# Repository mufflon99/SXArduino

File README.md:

# SX2Arduino
Lesen und Schreiben von SX1, SX2 und DCC Loks,
basiert auf der Libary von Gerard van der Sel.
Für das SX2 Interface wird ein Arduino Mega oder Arduino Due benötigt.
Serrvo Decoder zum Einbau in Signalschacht mit Arduino Nano
(SX is an open Model Railroad Control System, standardized in NEM 680 and NEM 681, Selectrix is a Trademark of TRIX - now owned by Maerklin)

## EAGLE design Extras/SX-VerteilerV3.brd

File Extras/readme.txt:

Für denen Nano Servo Decoder wird die Einspeise Platine SX Verteiler benötigt.

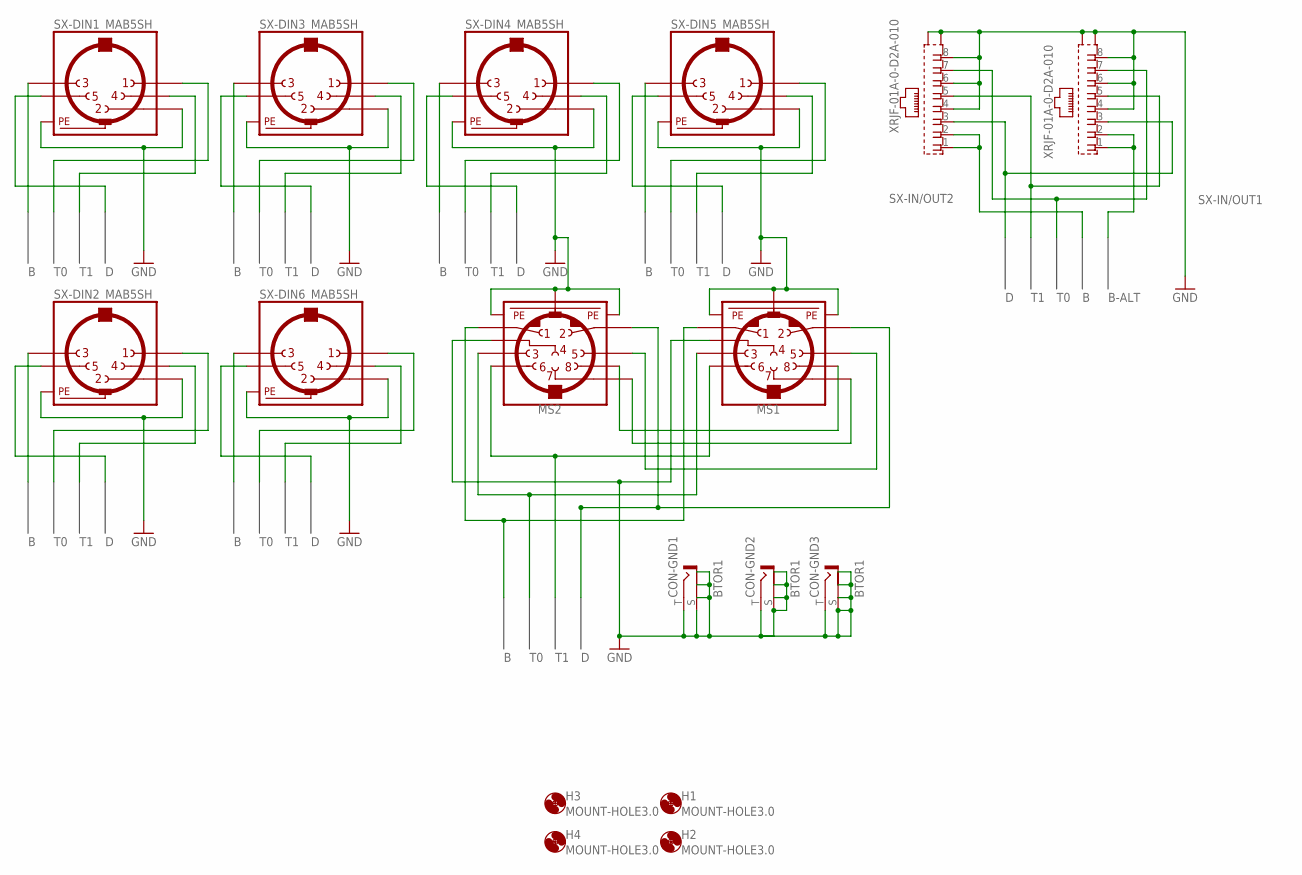
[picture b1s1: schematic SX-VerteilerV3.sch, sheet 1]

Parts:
CON-GND1, CON-GND2, CON-GND3: BTOR1
H1, H2, H3, H4: MOUNT-HOLE3.0; 3,0
MS1, MS2: MINI_DIN_8; M_DIN8
SX-DIN1, SX-DIN2, SX-DIN3, SX-DIN4, SX-DIN5, SX-DIN6: MAB5SH
SX-IN/OUT1, SX-IN/OUT2: XRJF-01A-0-D2A-010

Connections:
B: MS1.1, MS2.1, SX-DIN1.3, SX-DIN2.3, SX-DIN3.3, SX-DIN4.3, SX-DIN5.3, SX-DIN6.3, SX-IN/OUT2.1, SX-IN/OUT2.2; also elsewhere on the board
B-ALT: SX-IN/OUT1.1, SX-IN/OUT1.2; also elsewhere on the board
D: MS1.2, MS2.2, SX-DIN1.5, SX-DIN2.5, SX-DIN3.5, SX-DIN4.5, SX-DIN5.5, SX-DIN6.5, SX-IN/OUT1.3, SX-IN/OUT2.3; also elsewhere on the board
GND: CON-GND1.S (2), CON-GND1.S@1 (2), CON-GND1.S@2 (2), CON-GND1.S@3 (2), CON-GND1.T (1), CON-GND2.S (2), CON-GND2.S@1 (2), CON-GND2.S@2 (2), CON-GND2.S@3 (2), CON-GND2.T (1), CON-GND3.S (2), CON-GND3.S@1 (2), CON-GND3.S@2 (2), CON-GND3.S@3 (2), CON-GND3.T (1), MS1.4, MS1.SH1 (PE1), MS1.SH2 (PE2), MS1.SH3 (PE3), MS2.4, MS2.SH1 (PE1), MS2.SH2 (PE2), MS2.SH3 (PE3), SX-DIN1.2, SX-DIN1.PE, SX-DIN1.PE@ (PE), SX-DIN2.2, SX-DIN2.PE, SX-DIN2.PE@ (PE), SX-DIN3.2, SX-DIN3.PE, SX-DIN3.PE@ (PE), SX-DIN4.2, SX-DIN4.PE, SX-DIN4.PE@ (PE), SX-DIN5.2, SX-DIN5.PE, SX-DIN5.PE@ (PE), SX-DIN6.2, SX-DIN6.PE, SX-DIN6.PE@ (PE), SX-IN/OUT1.4, SX-IN/OUT1.6, SX-IN/OUT1.8, SX-IN/OUT1.S1 (S), SX-IN/OUT1.S2 (S), SX-IN/OUT2.4, SX-IN/OUT2.6, SX-IN/OUT2.8, SX-IN/OUT2.S1 (S), SX-IN/OUT2.S2 (S); also elsewhere on the board
unnamed: MS1.8, MS2.8
unnamed: MS1.7, MS2.7
unnamed: MS1.5, MS2.5
T0: MS1.3, MS2.3, SX-DIN1.1, SX-DIN2.1, SX-DIN3.1, SX-DIN4.1, SX-DIN5.1, SX-DIN6.1, SX-IN/OUT1.7, SX-IN/OUT2.7; also elsewhere on the board
T1: MS1.6, MS2.6, SX-DIN1.4, SX-DIN2.4, SX-DIN3.4, SX-DIN4.4, SX-DIN5.4, SX-DIN6.4, SX-IN/OUT1.5, SX-IN/OUT2.5; also elsewhere on the board

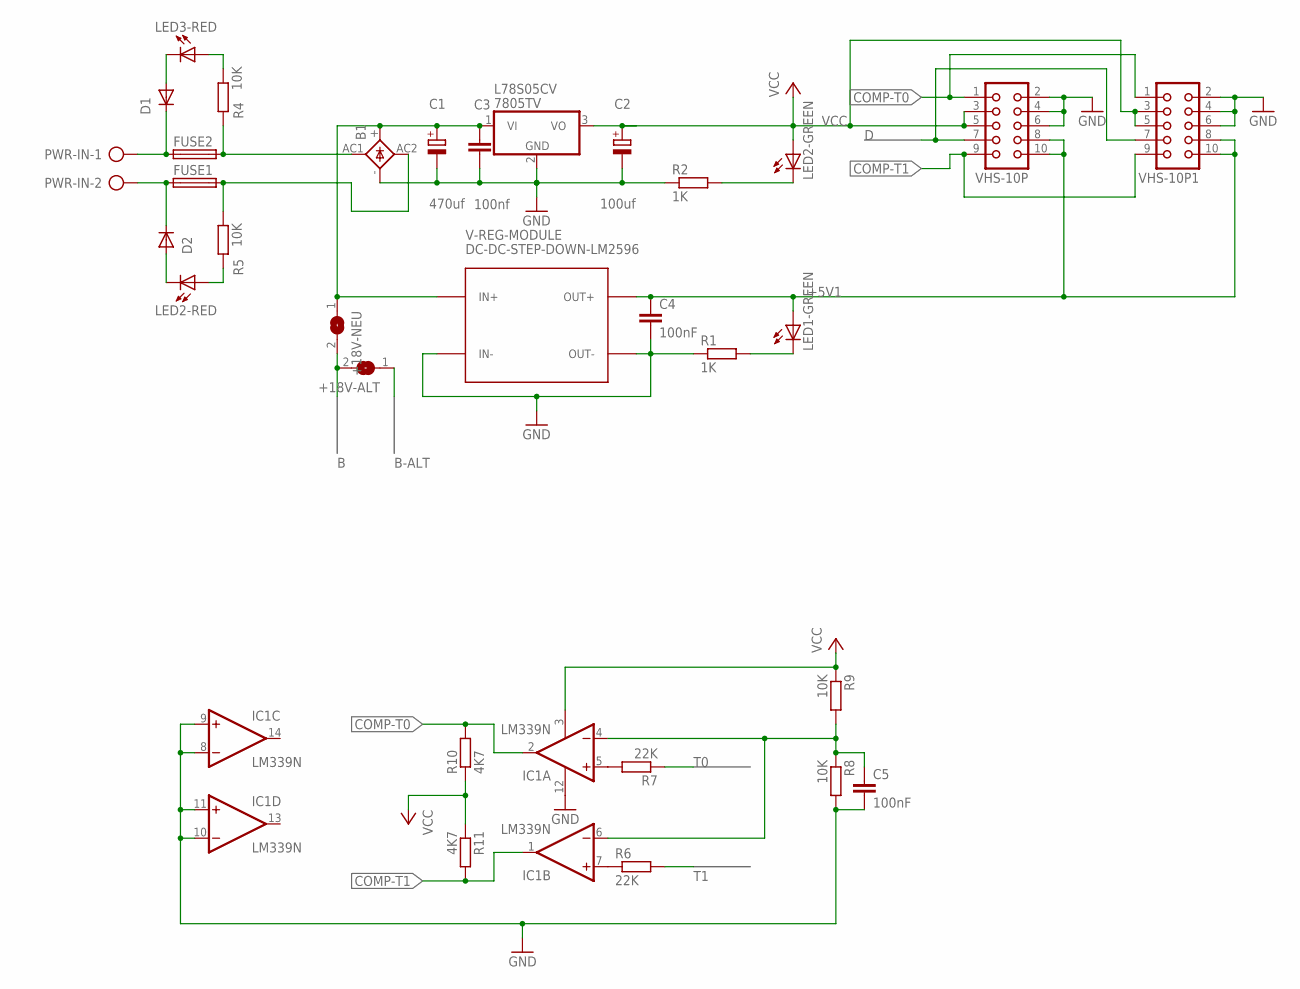
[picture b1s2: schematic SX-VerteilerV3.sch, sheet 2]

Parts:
+18V-ALT, +18V-NEU: SJW
B1: KBU
C1: 470uf; E5-13
C2: 100uf; E3,5-8
C3: 100nf; C0805
C4, C5: 100nF; C0805
D1, D2: PMLL4150; SOD80C
FUSE1, FUSE2: FUSEBLANK_5X20MM; FUSE_HOLDER_5X20MM
IC1: LM339N; DIL14
L78S05CV: 7805TV; TO220V
LED1-GREEN, LED2-GREEN, LED2-RED, LED3-RED: LED3MM
PWR-IN: AK300/2
R1, R2: 1K; R0805
R4, R5, R8, R9: 10K; R0805
R6, R7: 22K; R0805
R10, R11: 4K7; R0805
V-REG-MODULE: DC-DC-STEP-DOWN-LM2596
VHS-10P, VHS-10P1: CON10

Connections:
+5V1: C4.1, LED1-GREEN.A, V-REG-MODULE.OUT+, VHS-10P.8, VHS-10P.10, VHS-10P1.8, VHS-10P1.10
B: +18V-ALT.2, +18V-NEU.2; also elsewhere on the board
B-ALT: +18V-ALT.1; also elsewhere on the board
COMP-T0: IC1.2 (OUT), R10.2, VHS-10P.1, VHS-10P1.1
COMP-T1: IC1.1 (OUT), R11.2, VHS-10P.9, VHS-10P1.9
D: VHS-10P.7, VHS-10P1.7; also elsewhere on the board
GND: B1.-, C1.-, C2.-, C3.2, C4.2, C5.2, IC1.8 (-IN), IC1.9 (+IN), IC1.10 (-IN), IC1.11 (+IN), IC1.12 (GND), L78S05CV.2 (GND), R1.1, R2.1, R8.2, V-REG-MODULE.IN-, V-REG-MODULE.OUT-, VHS-10P.2, VHS-10P.4, VHS-10P.6, VHS-10P1.2, VHS-10P1.4, VHS-10P1.6; also elsewhere on the board
unnamed: D1.C, FUSE2.1, PWR-IN.1
unnamed: D2.C, FUSE1.1, PWR-IN.2
unnamed: B1.AC1, FUSE2.2, R4.1
unnamed: B1.AC2, FUSE1.2, R5.2
unnamed: D1.A, LED3-RED.K (C)
unnamed: IC1.5 (+IN), R7.2
unnamed: LED2-GREEN.K (C), R2.2
unnamed: IC1.7 (+IN), R6.1
unnamed: LED1-GREEN.K (C), R1.2
unnamed: LED3-RED.A, R4.2
unnamed: C5.1, IC1.4 (-IN), IC1.6 (-IN), R8.1, R9.2
unnamed: D2.A, LED2-RED.K (C)
unnamed: LED2-RED.A, R5.1
unnamed: +18V-NEU.1, B1.+, C1.+, C3.1, L78S05CV.1 (VI), V-REG-MODULE.IN+
T0: R7.1; also elsewhere on the board
T1: R6.2; also elsewhere on the board
VCC: C2.+, IC1.3 (V+), L78S05CV.3 (VO), LED2-GREEN.A, R9.1, R10.1, R11.1, VHS-10P.3, VHS-10P.5, VHS-10P1.3, VHS-10P1.5

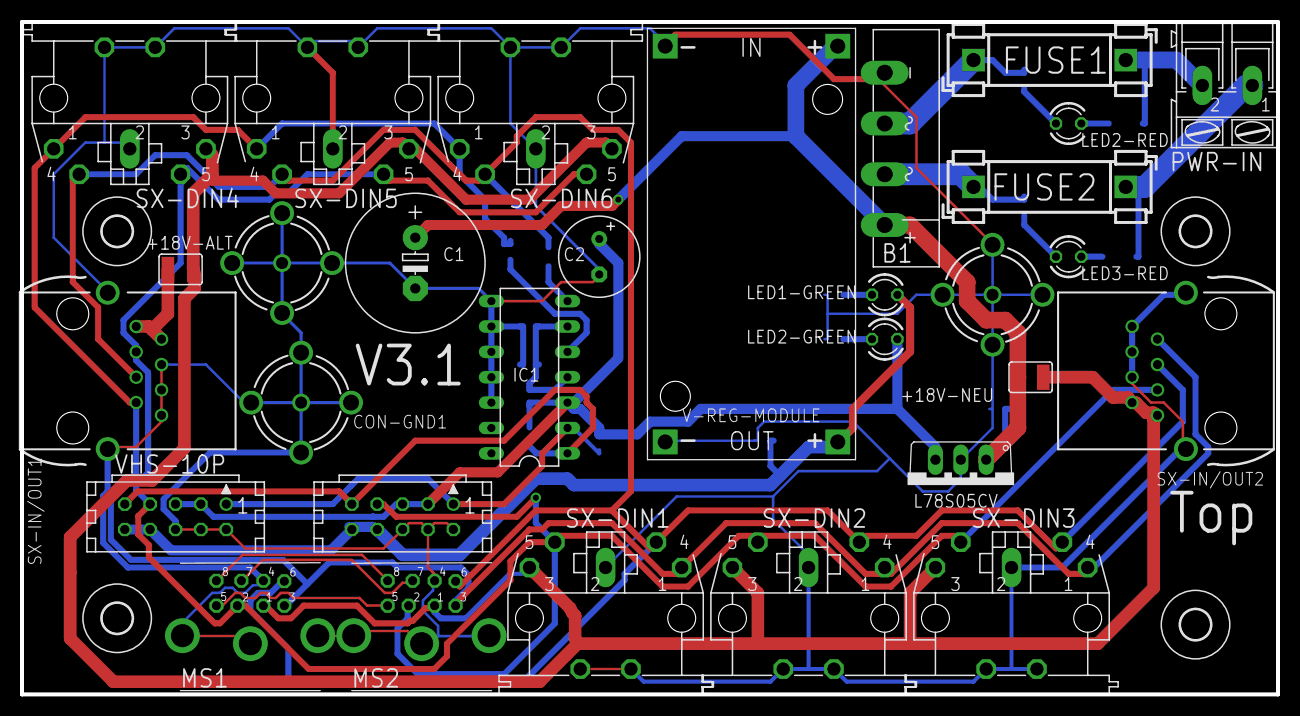
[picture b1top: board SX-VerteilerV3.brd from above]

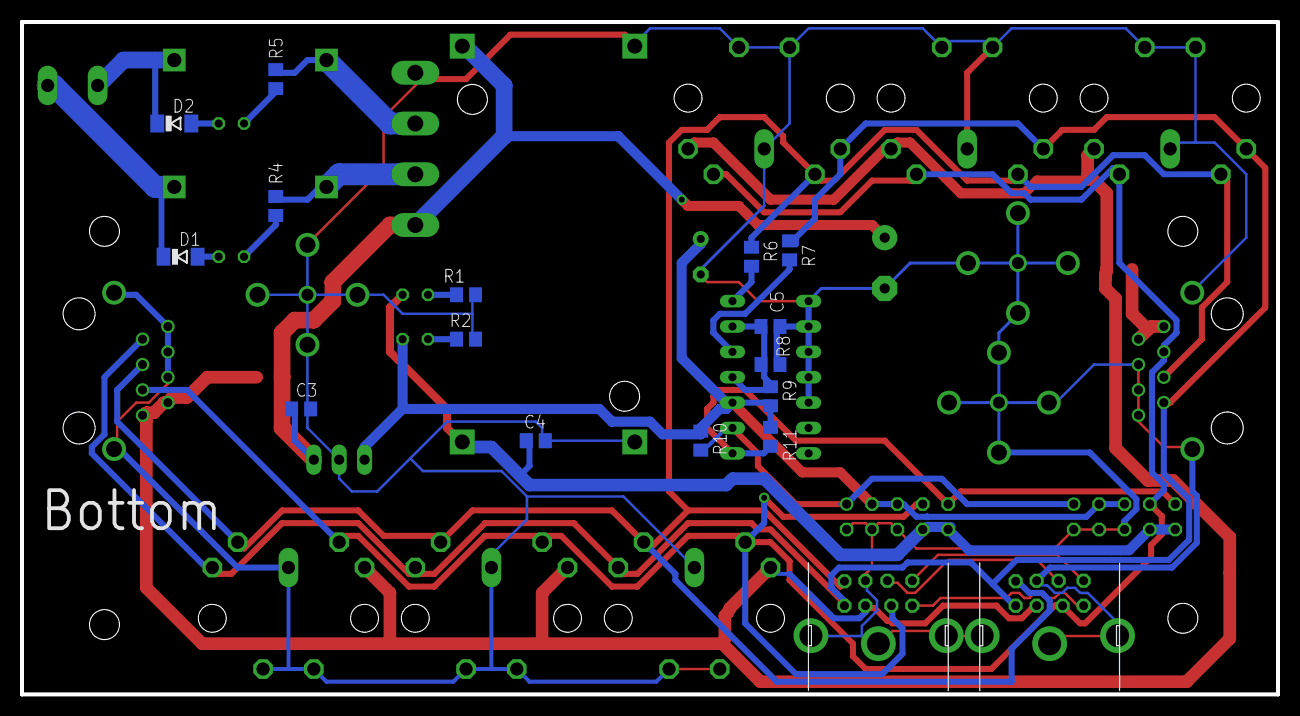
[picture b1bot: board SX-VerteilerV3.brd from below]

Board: 2 copper layers, 125.7 x 67.3 mm, 49 parts (15 on the bottom side), 27 nets.

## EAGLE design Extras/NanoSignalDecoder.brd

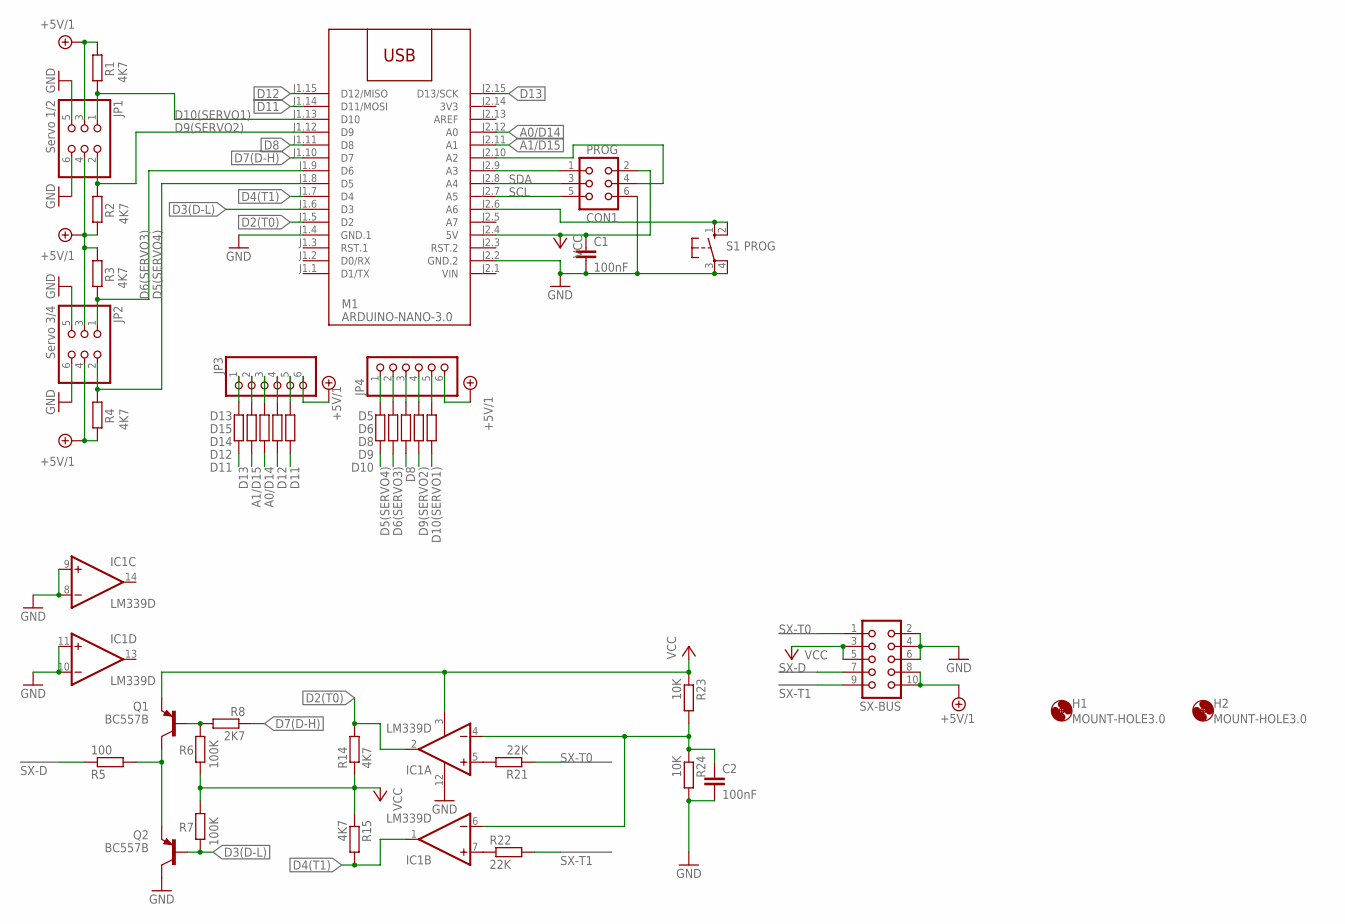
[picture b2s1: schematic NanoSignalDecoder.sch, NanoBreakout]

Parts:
C1, C2: 100nF; C0805
CON1: PROG; CON06
D5, D6, D8, D9, D10, D11, D12, D13, D14, D15: 500; R0805
H1, H2: MOUNT-HOLE3.0; 3,0
IC1: LM339D; SO14
JP1: Servo 1/2; 2X03/90
JP2: Servo 3/4; 2X03/90
JP3, JP4: PINHD-1X6; 1X06
M1: ARDUINO-NANO-3.0
Q1, Q2: BC557B; TO92-EBC
R1, R2, R3, R4, R14, R15: 4K7; R0805
R5: 100; R0805
R6, R7: 100K; R0805
R8: 2K7; R0805
R21, R22: 22K; R0805
R23, R24: 10K; R0805
S1: PROG; B3F-10XX
SX-BUS: CON10

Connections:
3V3: M1.J2.14 (3V3)
+5V/1: JP1.3, JP1.4, JP2.3, JP2.4, JP3.6, JP4.6, R1.1, R2.2, R3.1, R4.2, SX-BUS.8, SX-BUS.10
A0/D14: D14.1, M1.J2.12 (A0)
A1/D15: D15.1, M1.J2.11 (A1)
D2(T0): IC1.2 (OUT), M1.J1.5 (D2), R14.2
D3(D-L): M1.J1.6 (D3), Q2.B, R7.2
D4(T1): IC1.1 (OUT), M1.J1.7 (D4), R15.2
D5(SERVO4): D5.1, JP2.2, M1.J1.8 (D5), R4.1
D6(SERVO3): D6.1, JP2.1, M1.J1.9 (D6), R3.2
D7(D-H): M1.J1.10 (D7), R8.1
D8: D8.1, M1.J1.11 (D8)
D9(SERVO2): D9.1, JP1.2, M1.J1.12 (D9), R2.1
D10(SERVO1): D10.1, JP1.1, M1.J1.13 (D10), R1.2
D11: D11.1, M1.J1.14 (D11/MOSI)
D12: D12.1, M1.J1.15 (D12/MISO)
D13: D13.1, M1.J2.15 (D13/SCK)
GND: C1.2, C2.2, CON1.6, IC1.8 (-IN), IC1.9 (+IN), IC1.10 (-IN), IC1.11 (+IN), IC1.12 (GND), JP1.5, JP1.6, JP2.5, JP2.6, M1.J1.4 (GND.1), M1.J2.2 (GND.2), Q2.C, R24.2, S1.3, S1.4 (P1), SX-BUS.2, SX-BUS.4, SX-BUS.6
unnamed: D8.2, JP4.3
unnamed: D5.2, JP4.1
unnamed: D13.2, JP3.1
unnamed: D6.2, JP4.2
unnamed: D15.2, JP3.2
unnamed: C2.1, IC1.4 (-IN), IC1.6 (-IN), R23.2, R24.1
unnamed: Q1.C, Q2.E, R5.1
unnamed: D9.2, JP4.4
unnamed: D10.2, JP4.5
unnamed: D14.2, JP3.3
unnamed: D12.2, JP3.4
unnamed: D11.2, JP3.5
unnamed: Q1.B, R6.1, R8.2
unnamed: M1.J2.6 (A6), S1.1 (S), S1.2 (S1)
unnamed: CON1.1, M1.J2.9 (A3)
unnamed: CON1.4, M1.J2.10 (A2)
unnamed: IC1.5 (+IN), R21.2
unnamed: IC1.7 (+IN), R22.1
SCL: CON1.5, M1.J2.7 (A5)
SDA: CON1.3, M1.J2.8 (A4)
SX-D: R5.2, SX-BUS.7
SX-T0: R21.1, SX-BUS.1
SX-T1: R22.2, SX-BUS.9
VCC: C1.1, CON1.2, IC1.3 (V+), M1.J2.4 (5V), Q1.E, R6.2, R7.1, R14.1, R15.1, R23.1, SX-BUS.3, SX-BUS.5
VIN: M1.J2.1 (VIN)

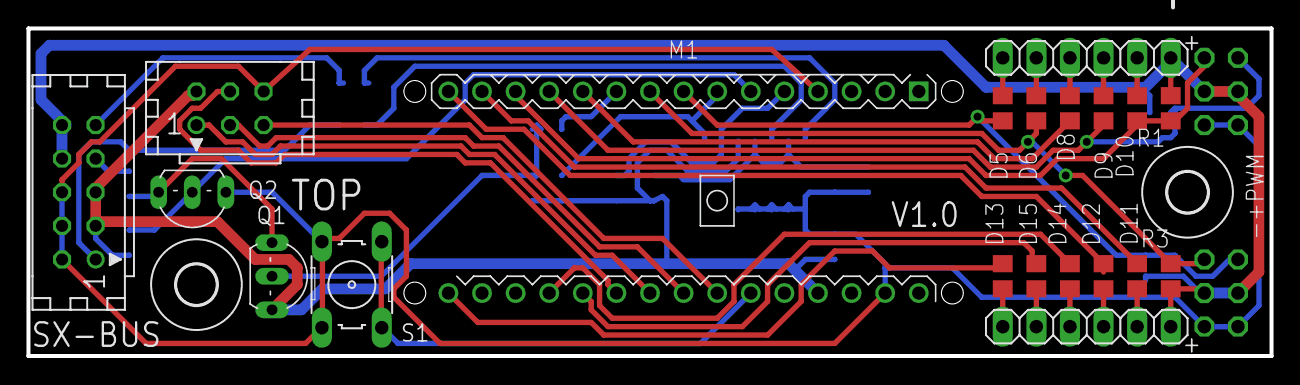
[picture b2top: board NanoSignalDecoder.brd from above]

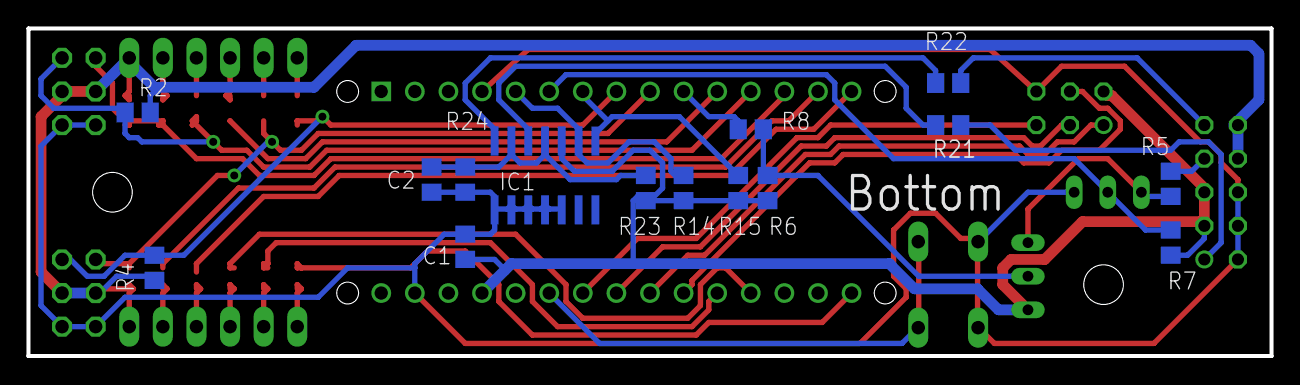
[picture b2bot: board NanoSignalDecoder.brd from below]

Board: 2 copper layers, 94.0 x 24.8 mm, 39 parts (15 on the bottom side), 40 nets.

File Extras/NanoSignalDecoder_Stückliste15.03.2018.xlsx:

VHS Servo Platine Parts
Part | Value | Package | Bemerkungen
C1,C2 | 100nF | SMD 0805
R1-R4, R14,R15 | 4K7 | SMD 0805
R5 | 100 | SMD 0805
R6-R7 | 100K | SMD 0805
R8 | 2K7 | SMD 0805
R21,R22 | 22K | SMD 0805
R23,R24,R25 | 10K | SMD 0805 | R25 zwischen Arduino PIN A7 und 5V einlöten, Lötbrücke A7/A6 herstellen
Q1,Q2 | BC557B | TO92
IC1 | LM339D | SO14 | Achtung: Beschriftung umgedreht zur Platinenbeschriftung! Pin 1 beachten!
S1 | B3F-10XX
JP1,JP2 | RM 2,54 | PINHD-2X3/90 Grad
M1 | Arduino Nano V3.0 , ggf auf IC Pins und Sockel montieren
VHS Servo Einstellplatine Parts
Part | Bemerkungen |  |  | Shop
Display | CP02013 | I2C 1602 HD44780, Adr: 0x27 |  | +++
Rotary Encoder | EC11-15mm |  |  | www.tindie.com/products/Saimon/i2c-encoder-connect-rotary-encoders-on-i2c-bus/
I2C Roary | I2C Encoder
LED | Bi-Colour
Drehschalter | CKA1X12 | 1x12 Kontakte,6mm Achse |  | www.pollin.de |  | 420924
Dreknopf | CLIFF CL1 | Mit Zeigermakierung,geriffelt |  |  |  | 410110
Drehknopf |  | 16x14mm Schwarz |  |  |  | 410176
Taster |  | Minatur Drucktaster |  |  |  | 420322

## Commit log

2018-09-01 Add files via upload
    Selectrix Libary zum Lesen und Schreiben von zwei SX Bussen an einem Arduino mit Atmega 328.
    Des weiteren werden SX Bus Eweiterungen für SX2/DCC Loks unterstützt.
    Achtung: Momentan noch Alpha Status.
    (SX is an open Model Railroad Control System, standardized in NEM 680 and NEM 681, Selectrix is a Trademark of TRIX - now owned by Maerklin)
2018-09-01 Rename Examples/Interface.ino to Examples/SX2/Interface.ino
2018-09-01 Rename Examples/Read me.txt to Examples/SX2/Read me.txt
2018-09-06 Update SX2Arduino.cpp
    Some Bug Fixes, Arduino Mega now supported
2018-09-06 Update SX2Arduino.h
    Arduino Mega supported
2018-09-06 Update Interface.ino
    Arduino Mega should now work out of the box
2018-09-06 Update SX2ArduinoTest.ino
    Bug Fixes
2018-09-19 Update SX2Arduino.cpp
    Now Arduino Mega and Arduino Due supported.
2018-09-19 Create Interface.ino
    See readme.txt!
    Sx2 Interface for Arudio Mega or Due
2018-09-19 Create SX2ArduinoTest.ino
    There is still a bug in returning Adress.
2018-09-19 Create Servo.ino
    First release, see Extras for Hardware Description

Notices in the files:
parts and their libraries:
diy-modules: Released under the Creative Commons Attribution 4.0 International License: http://creativecommons.org/licenses/by/4.0
